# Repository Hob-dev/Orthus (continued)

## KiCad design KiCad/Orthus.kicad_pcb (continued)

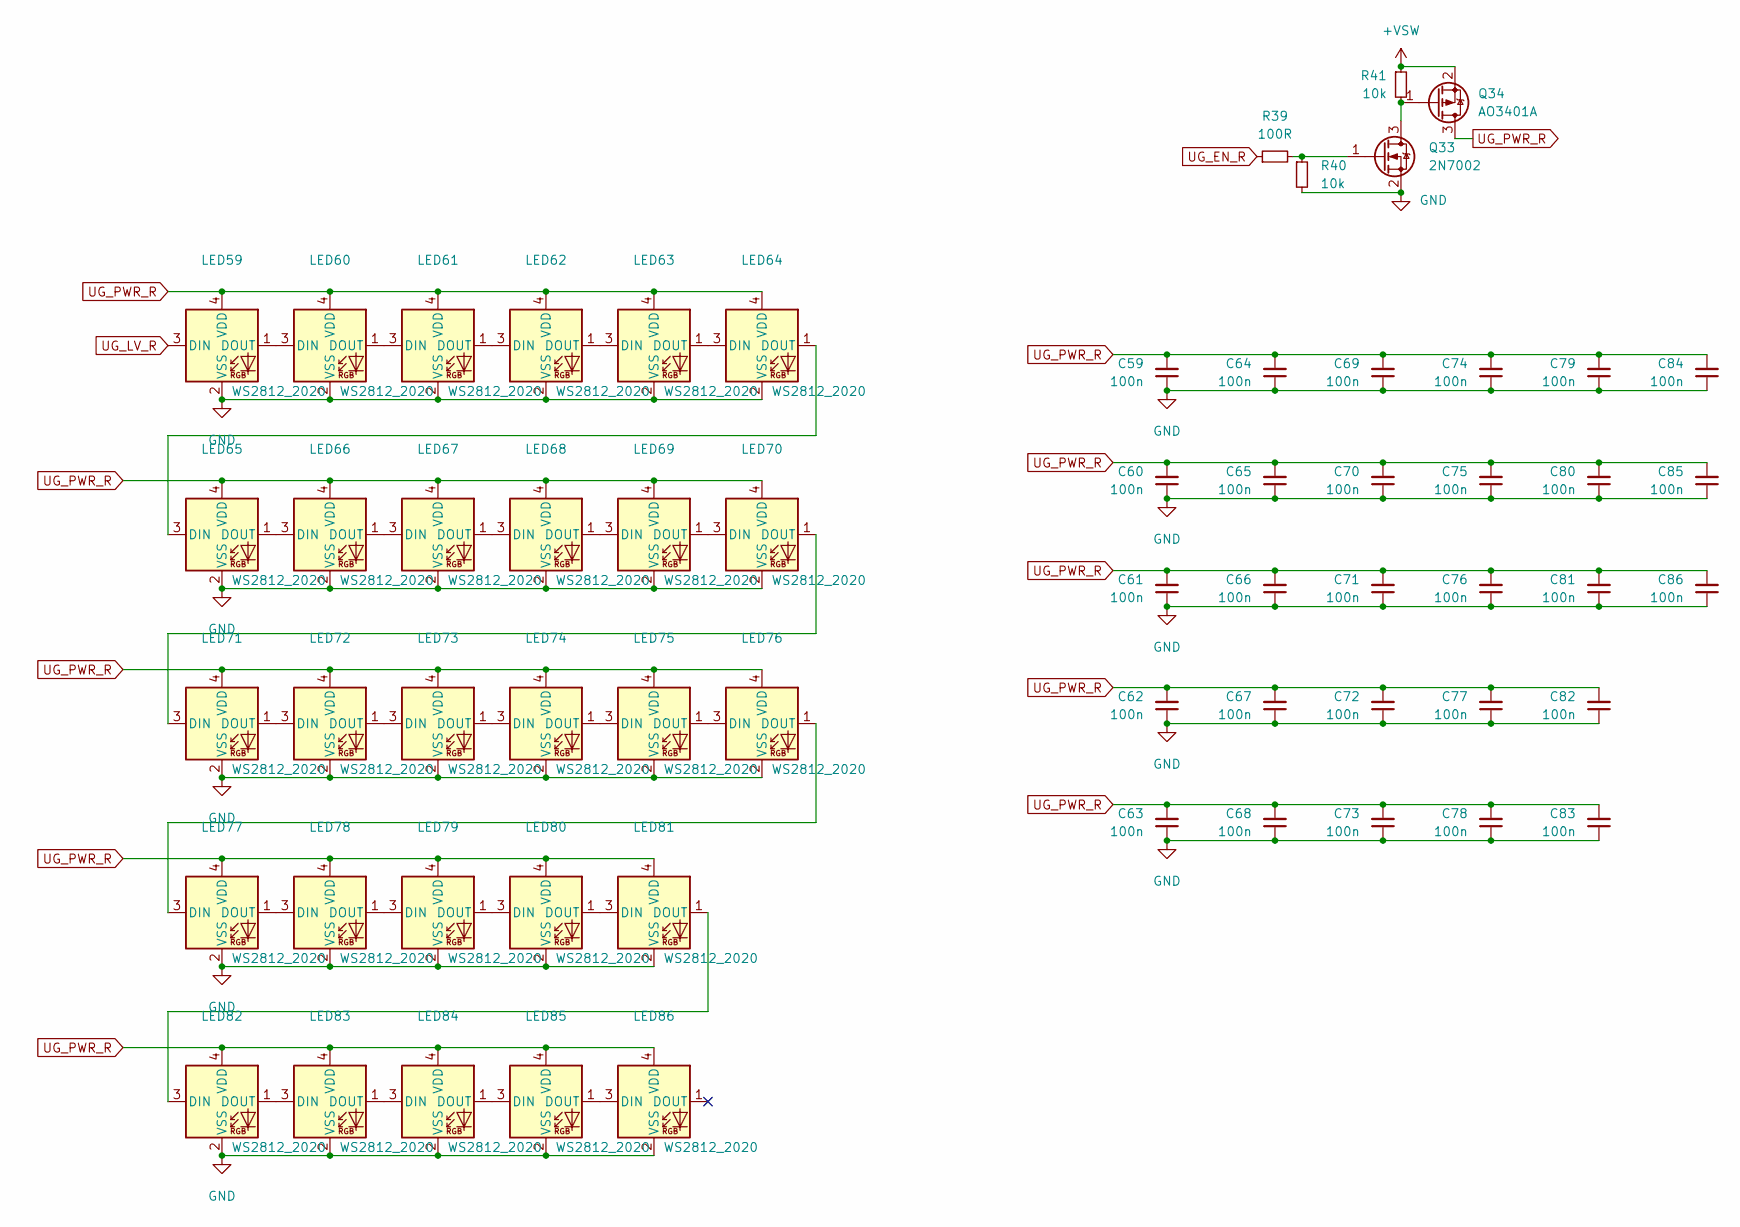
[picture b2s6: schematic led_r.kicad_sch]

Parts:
C59, C60, C61, C62, C63, C64, C65, C66, C67, C68, C69, C70, C71, C72, C73, C74, C75, C76, C77, C78, C79, C80, C81, C82, C83, C84, C85, C86: 100n; C_0402_1005Metric
LED59, LED60, LED61, LED62, LED63, LED64, LED65, LED66, LED67, LED68, LED69, LED70, LED71, LED72, LED73, LED74, LED75, LED76, LED77, LED78, LED79, LED80, LED81, LED82, LED83, LED84, LED85, LED86: WS2812_2020; YS-SK6812MINI-E
Q33: 2N7002; SOT-23
Q34: AO3401A; SOT-23
R39: 100R; R_0402_1005Metric
R40, R41: 10k; R_0402_1005Metric

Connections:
+VSW: Q34.2 (S), R41.1; also elsewhere on the board
GND: C59.1, C60.1, C61.1, C62.1, C63.1, C64.1, C65.1, C66.1, C67.1, C68.1, C69.1, C70.1, C71.1, C72.1, C73.1, C74.1, C75.1, C76.1, C77.1, C78.1, C79.1, C80.1, C81.1, C82.1, C83.1, C84.1, C85.1, C86.1, LED59.2 (VSS), LED60.2 (VSS), LED61.2 (VSS), LED62.2 (VSS), LED63.2 (VSS), LED64.2 (VSS), LED65.2 (VSS), LED66.2 (VSS), LED67.2 (VSS), LED68.2 (VSS), LED69.2 (VSS), LED70.2 (VSS), LED71.2 (VSS), LED72.2 (VSS), LED73.2 (VSS), LED74.2 (VSS), LED75.2 (VSS), LED76.2 (VSS), LED77.2 (VSS), LED78.2 (VSS), LED79.2 (VSS), LED80.2 (VSS), LED81.2 (VSS), LED82.2 (VSS), LED83.2 (VSS), LED84.2 (VSS), LED85.2 (VSS), LED86.2 (VSS), Q33.2 (S), R40.2; also elsewhere on the board
unnamed: LED59.1 (DOUT), LED60.3 (DIN)
unnamed: LED60.1 (DOUT), LED61.3 (DIN)
unnamed: LED61.1 (DOUT), LED62.3 (DIN)
unnamed: LED62.1 (DOUT), LED63.3 (DIN)
unnamed: LED63.1 (DOUT), LED64.3 (DIN)
unnamed: LED64.1 (DOUT), LED65.3 (DIN)
unnamed: LED65.1 (DOUT), LED66.3 (DIN)
unnamed: LED66.1 (DOUT), LED67.3 (DIN)
unnamed: LED67.1 (DOUT), LED68.3 (DIN)
unnamed: LED68.1 (DOUT), LED69.3 (DIN)
unnamed: LED69.1 (DOUT), LED70.3 (DIN)
unnamed: LED70.1 (DOUT), LED71.3 (DIN)
unnamed: LED71.1 (DOUT), LED72.3 (DIN)
unnamed: LED72.1 (DOUT), LED73.3 (DIN)
unnamed: LED73.1 (DOUT), LED74.3 (DIN)
unnamed: LED74.1 (DOUT), LED75.3 (DIN)
unnamed: LED75.1 (DOUT), LED76.3 (DIN)
unnamed: LED76.1 (DOUT), LED77.3 (DIN)
unnamed: LED77.1 (DOUT), LED78.3 (DIN)
unnamed: LED78.1 (DOUT), LED79.3 (DIN)
unnamed: LED79.1 (DOUT), LED80.3 (DIN)
unnamed: LED80.1 (DOUT), LED81.3 (DIN)
unnamed: LED81.1 (DOUT), LED82.3 (DIN)
unnamed: LED82.1 (DOUT), LED83.3 (DIN)
unnamed: LED83.1 (DOUT), LED84.3 (DIN)
unnamed: LED84.1 (DOUT), LED85.3 (DIN)
unnamed: LED85.1 (DOUT), LED86.3 (DIN)
unnamed: Q33.3 (D), Q34.1 (G), R41.2
unnamed: Q33.1 (G), R39.2, R40.1
UG_EN_R: R39.1
UG_LV_R: LED59.3 (DIN)
UG_PWR_R: C59.2, C60.2, C61.2, C62.2, C63.2, C64.2, C65.2, C66.2, C67.2, C68.2, C69.2, C70.2, C71.2, C72.2, C73.2, C74.2, C75.2, C76.2, C77.2, C78.2, C79.2, C80.2, C81.2, C82.2, C83.2, C84.2, C85.2, C86.2, LED59.4 (VDD), LED60.4 (VDD), LED61.4 (VDD), LED62.4 (VDD), LED63.4 (VDD), LED64.4 (VDD), LED65.4 (VDD), LED66.4 (VDD), LED67.4 (VDD), LED68.4 (VDD), LED69.4 (VDD), LED70.4 (VDD), LED71.4 (VDD), LED72.4 (VDD), LED73.4 (VDD), LED74.4 (VDD), LED75.4 (VDD), LED76.4 (VDD), LED77.4 (VDD), LED78.4 (VDD), LED79.4 (VDD), LED80.4 (VDD), LED81.4 (VDD), LED82.4 (VDD), LED83.4 (VDD), LED84.4 (VDD), LED85.4 (VDD), LED86.4 (VDD), Q34.3 (D)

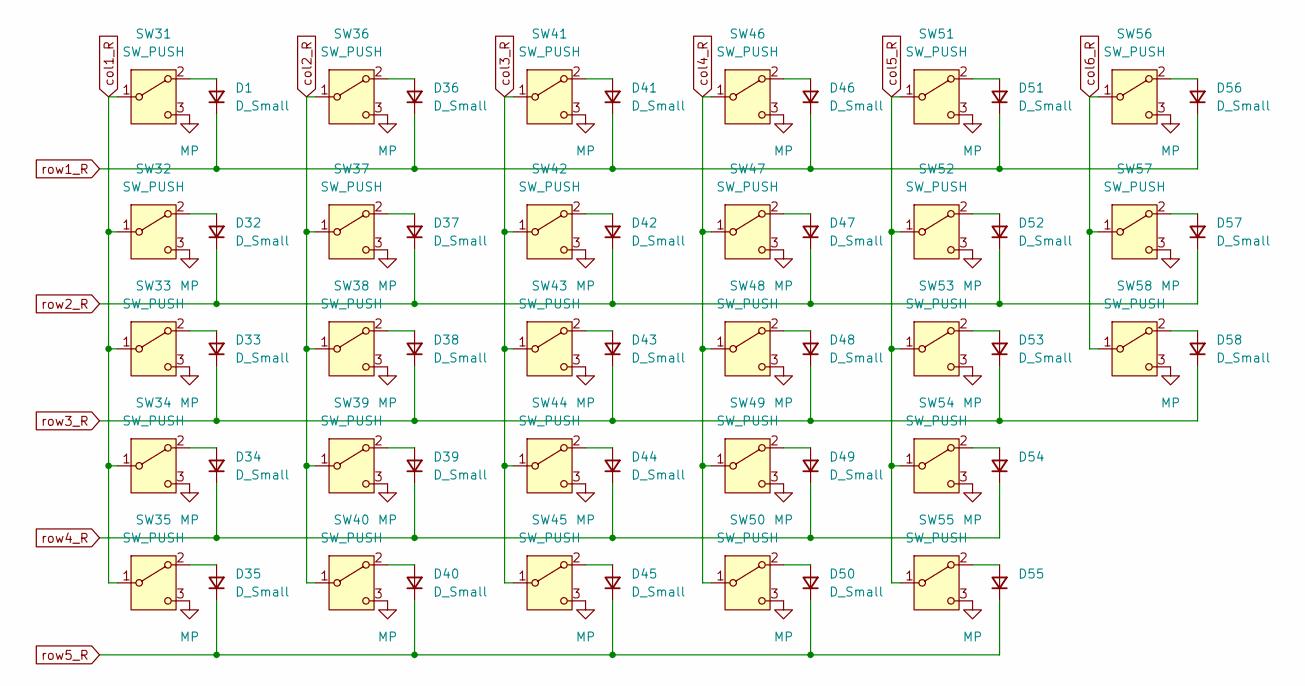
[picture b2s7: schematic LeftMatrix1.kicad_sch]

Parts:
D1, D32, D33, D34, D35, D36, D37, D38, D39, D40, D41, D42, D43, D44, D45, D46, D47, D48, D49, D50, D51, D52, D53, D54, D55, D56, D57, D58: D_Small; D_SOD-123
SW31, SW32, SW33, SW34, SW35, SW36, SW37, SW38, SW39, SW40, SW41, SW42, SW43, SW44, SW45, SW46, SW47, SW48, SW49, SW50, SW51, SW52, SW53, SW54, SW55, SW56, SW57, SW58: SW_PUSH; HOB_CHOC_V1&V2

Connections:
unnamed: D32.2 (A), SW32.2 (A)
unnamed: D33.2 (A), SW33.2 (A)
unnamed: D34.2 (A), SW34.2 (A)
unnamed: D35.2 (A), SW35.2 (A)
unnamed: D36.2 (A), SW36.2 (A)
unnamed: D37.2 (A), SW37.2 (A)
unnamed: D38.2 (A), SW38.2 (A)
unnamed: D39.2 (A), SW39.2 (A)
unnamed: D40.2 (A), SW40.2 (A)
unnamed: D41.2 (A), SW41.2 (A)
unnamed: D42.2 (A), SW42.2 (A)
unnamed: D43.2 (A), SW43.2 (A)
unnamed: D44.2 (A), SW44.2 (A)
unnamed: D45.2 (A), SW45.2 (A)
unnamed: D46.2 (A), SW46.2 (A)
unnamed: D47.2 (A), SW47.2 (A)
unnamed: D48.2 (A), SW48.2 (A)
unnamed: D49.2 (A), SW49.2 (A)
unnamed: D50.2 (A), SW50.2 (A)
unnamed: D51.2 (A), SW51.2 (A)
unnamed: D52.2 (A), SW52.2 (A)
unnamed: D53.2 (A), SW53.2 (A)
unnamed: D54.2 (A), SW54.2 (A)
unnamed: D55.2 (A), SW55.2 (A)
unnamed: D56.2 (A), SW56.2 (A)
unnamed: D57.2 (A), SW57.2 (A)
unnamed: D58.2 (A), SW58.2 (A)
col1_R: SW31.1 (B), SW32.1 (B), SW33.1 (B), SW34.1 (B), SW35.1 (B); also elsewhere on the board
col2_R: SW36.1 (B), SW37.1 (B), SW38.1 (B), SW39.1 (B), SW40.1 (B); also elsewhere on the board
col3_R: SW41.1 (B), SW42.1 (B), SW43.1 (B), SW44.1 (B), SW45.1 (B); also elsewhere on the board
col4_R: SW46.1 (B), SW47.1 (B), SW48.1 (B), SW49.1 (B), SW50.1 (B); also elsewhere on the board
col5_R: SW51.1 (B), SW52.1 (B), SW53.1 (B), SW54.1 (B), SW55.1 (B); also elsewhere on the board
col6_R: SW56.1 (B), SW57.1 (B), SW58.1 (B); also elsewhere on the board
row2_R: D32.1 (K), D37.1 (K), D42.1 (K), D47.1 (K), D52.1 (K), D57.1 (K); also elsewhere on the board
row3_R: D33.1 (K), D38.1 (K), D43.1 (K), D48.1 (K), D53.1 (K), D58.1 (K); also elsewhere on the board
row4_R: D34.1 (K), D39.1 (K), D44.1 (K), D49.1 (K), D54.1 (K); also elsewhere on the board
row5_R: D35.1 (K), D40.1 (K), D45.1 (K), D50.1 (K), D55.1 (K); also elsewhere on the board

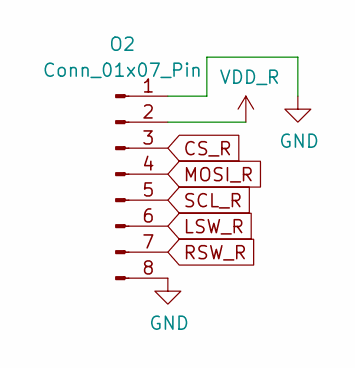
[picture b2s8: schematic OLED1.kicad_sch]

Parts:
O2: Conn_01x07_Pin; FPC-SMD_8P-P0.50_XUNPU_FPC-05F-8PH15

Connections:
CS_R: O2.3; also elsewhere on the board
GND: O2.1, O2.8; also elsewhere on the board
LSW_R: O2.6; also elsewhere on the board
MOSI_R: O2.4; also elsewhere on the board
RSW_R: O2.7; also elsewhere on the board
SCL_R: O2.5; also elsewhere on the board
VDD_R: O2.2; also elsewhere on the board

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
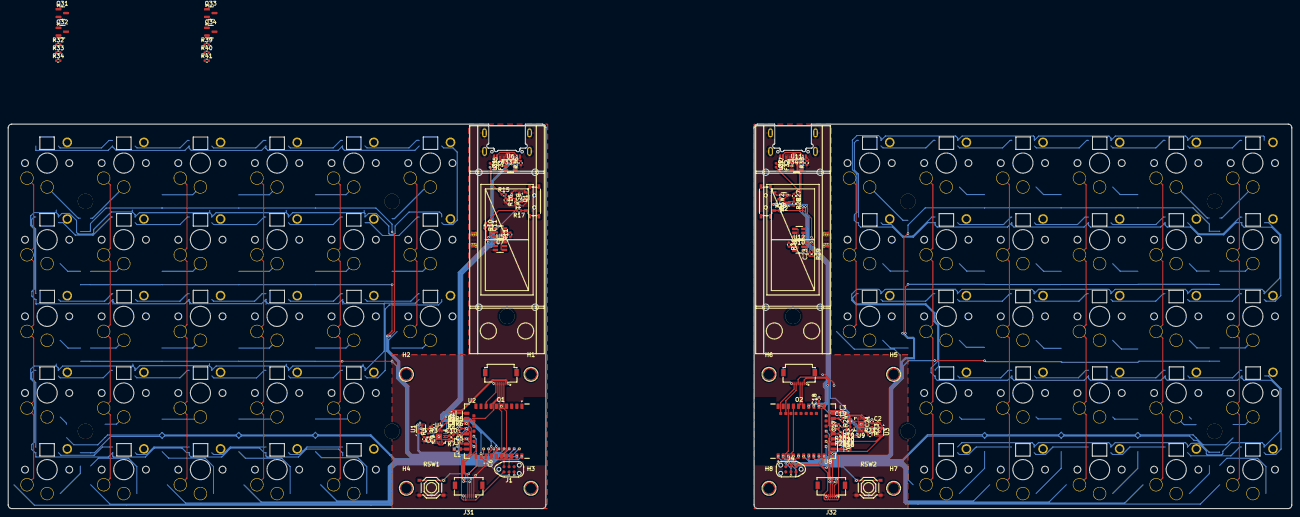
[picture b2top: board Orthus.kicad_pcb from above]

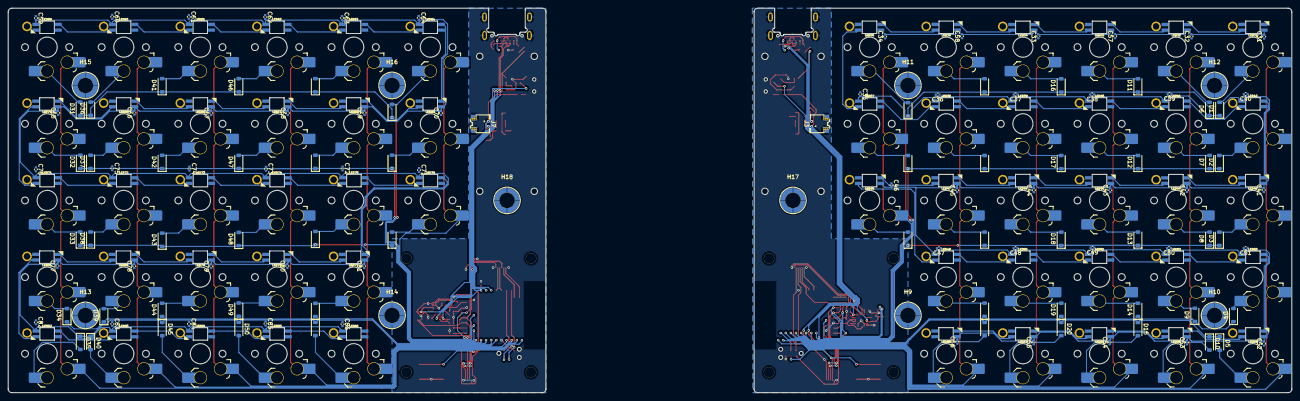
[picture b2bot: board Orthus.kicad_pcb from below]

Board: 2 copper layers, 319.0 x 95.6 mm, 336 parts (236 on the bottom side), 211 nets.

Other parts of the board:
D31: D_Small; D_SOD-123

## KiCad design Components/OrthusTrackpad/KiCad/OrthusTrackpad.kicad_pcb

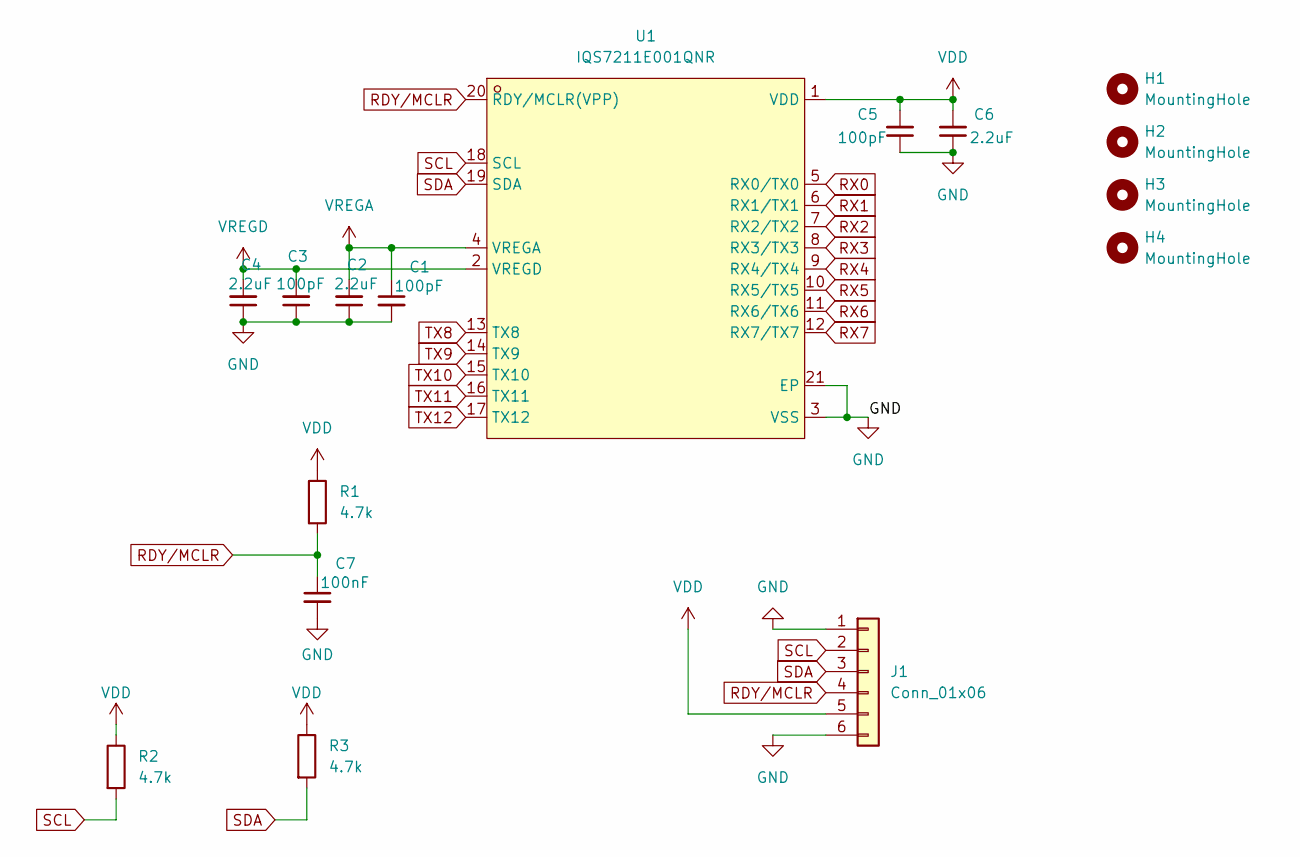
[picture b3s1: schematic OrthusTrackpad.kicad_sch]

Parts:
C1, C3, C5: 100pF; C_0402_1005Metric
C2, C4, C6: 2.2uF; C_0402_1005Metric
C7: 100nF; C_0402_1005Metric
H1, H2, H3, H4: MountingHole; SMD-1_SMTSO1620MTJ
J1: Conn_01x06; FPC-SMD_6P-P0.50_XUNPU_FPC-05F-6PH15
R1, R2, R3: 4.7k; R_0603_1608Metric
U1: IQS7211E001QNR; UQFN-20_L3.0-W3.0-P0.40-BL-EP1.7; LCSC Part C20179547

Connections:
GND: C1.2, C2.1, C3.1, C4.1, C5.1, C6.1, C7.2, J1.1, J1.6, U1.3 (VSS), U1.21 (EP)
RDY/MCLR: C7.1, J1.4, R1.2, U1.20 (RDY/MCLR(VPP))
RX0: U1.5 (RX0/TX0)
RX1: U1.6 (RX1/TX1)
RX2: U1.7 (RX2/TX2)
RX3: U1.8 (RX3/TX3)
RX4: U1.9 (RX4/TX4)
RX5: U1.10 (RX5/TX5)
RX6: U1.11 (RX6/TX6)
RX7: U1.12 (RX7/TX7)
SCL: J1.2, R2.2, U1.18 (SCL)
SDA: J1.3, R3.2, U1.19 (SDA)
TX8: U1.13 (TX8)
TX9: U1.14 (TX9)
TX10: U1.15 (TX10)
TX11: U1.16 (TX11)
TX12: U1.17 (TX12)
VDD: C5.2, C6.2, J1.5, R1.1, R2.1, R3.1, U1.1 (VDD)
VREGA: C1.1, C2.2, U1.4 (VREGA)
VREGD: C3.2, C4.2, U1.2 (VREGD)

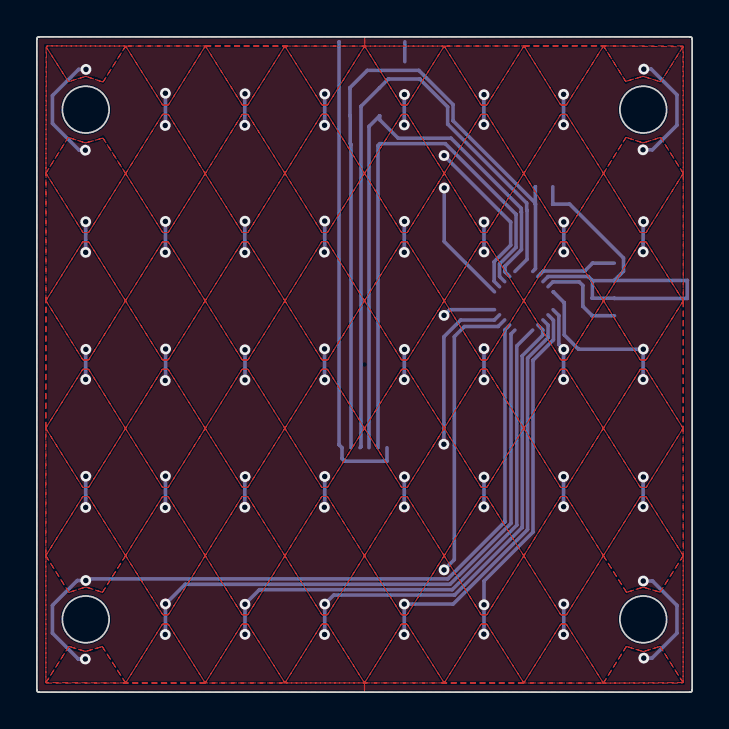
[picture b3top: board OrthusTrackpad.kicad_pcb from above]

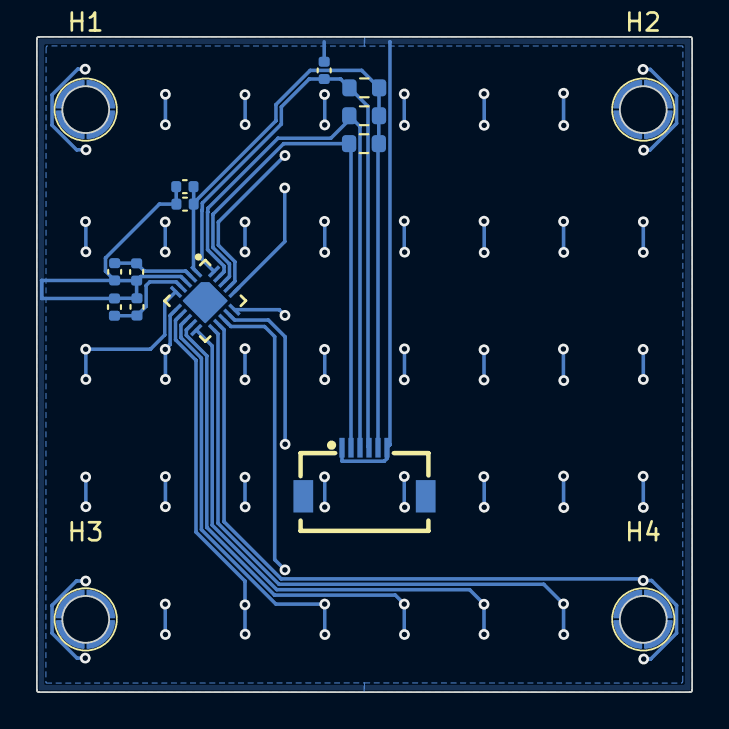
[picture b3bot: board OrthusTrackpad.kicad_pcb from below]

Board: 2 copper layers, 36.4 x 36.4 mm, 16 parts (16 on the bottom side), 7 nets.

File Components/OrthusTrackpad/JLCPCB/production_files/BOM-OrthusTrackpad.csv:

Comment,Designator,Footprint,LCSC,Quantity
100nF,C7,C_0402_1005Metric,C1525,1
100pF,"C1,C3,C5",C_0402_1005Metric,C1546,3
IQS7211E001QNR,U1,UQFN-20_L3.0-W3.0-P0.40-BL-EP1.7,C20179547,1
4.7k,"R1,R2,R3",R_0603_1608Metric,C23162,3
Conn_01x06,J1,FPC-SMD_6P-P0.50_XUNPU_FPC-05F-6PH15,C2856814,1
2.2uF,"C2,C4,C6",C_0402_1005Metric,C60078,3

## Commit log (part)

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2026-04-17 init commit
